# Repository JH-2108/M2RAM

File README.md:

# M2RAM 
A custom 128KB SRAM module designed using an M.2 form factor. 

# Overview 
M2RAM is an electronics project focused on designing and building a functional external memory expansion module. 

The project uses an AS6C1008 asynchronous SRAM chip mounted on a custom M.2 PCB. It is designed to communicate with an external host controller through a compatible memory interface. 

The project explores computer memory architecture, digital electronics, PCB designing and some parts of embedded programming. 

# Features 
- 128 KB asynchronous SRAM
- Custom M.2 2280 PCB
- 8-bit data bus
- 17-bit address bus
- External host-controller compatibility
- Custom memory read/write interface
- KiCAD-designed schematic and PCB

# Hardware 
| Components | Description |
|---|---|
| AS6C1008-55SIN | 128KB asynchronous SRAM | 
| 74HC595 | Shift registers for digital signal expansion | 
| M.2 edge connector | Physical module interface | 
| Capacitors | Power supply decoupling | 
| Resistors | Signal conditioning and pull ups | 

# How it works 
The SRAM stores data in an array of memory locations, with each location containing 8 bits. 

The host controller communicates with the memory through its address, data and control signals. 

The controller selects a memory address and performs read or write operations using the SRAM control interface. 

An external M.2 breakout adapter can be used to simplify development and testing. 

# M2RAM Breakout Adapter

A separate breakout adapter PCB was designed as a companion to the M2RAM memory module. 

The adapter provides a female M.2 M-key socket that accepts the M2RAM module through its gold edge contacts. 

Instead of requiring a host controller to connect directly to the M.2 connector, the adapter exposes the module's electrical interface through two rows of 2.54mm through-hole header connections. 

# Adapter features
- Female M.2 M-key socket for connecting the M2RAM module.
- 8 pin data interface exposing DQ0-DQ7
- 8 pin control and power interface
- 3.3V power and GND connections
- Decoupling capacitors for supply stability
- Through hole header connections for convenient wiring to external controllers.

# Adapter interface
|Header |pin|Signal|
|---|---|---|
|J2 | 1 | DQ0|
|J2 | 2 | DQ1|
|J2 | 3 | DQ2|
|J2 | 4 | DQ3|
|J2 | 5 | DQ4|
|J2 | 6 | DQ5|
|J2 | 7 | DQ6|
|J2 | 8 | DQ7|
|J3 | 1 | SRCLR|
|J3 | 2 | SRCLK|
|J3 | 3 | RCLK|
|J3 | 4 | U2SER|
|J3 | 5 | OE|
|J3 | 6 | +3V3|
|J3 | 7 | GND|
|J3 | 8 | GND|

The adapter does not contain additional SRAM or shift registers. It simple exposes the existing M2RAM module interface to external hardware. 

Note: The adapter is an optional development accessory. The M2RAM module can be used with a compatible custom host interface without this particular adapter. 

# Bill of Materials

Will be added later 

# Pictures of the M2RAM

**PCB design** 

**Top layer**

**Bottom layer**

**Schematics** 

**3D rendered PCB design** 

**Physical picture**

A photo will be added later

# Pictures of the M2RAM adapter

**PCB Design** 

**Top layer**

**Bottom layer**

**Schematics**

**3D rendered PCB**

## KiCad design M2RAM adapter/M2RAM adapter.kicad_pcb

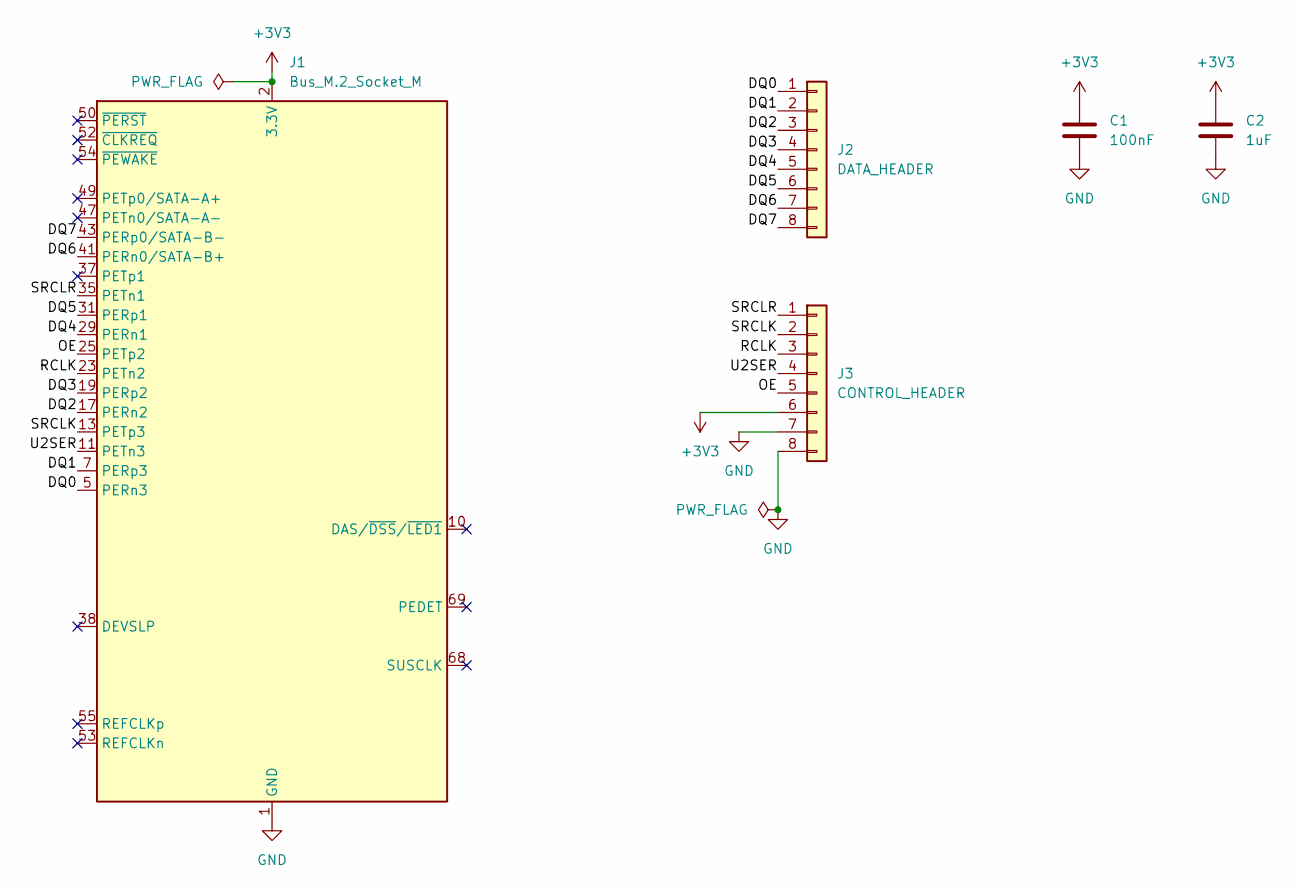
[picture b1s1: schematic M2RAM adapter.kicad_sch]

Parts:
C1: 100nF; C_Disc_D5.0mm_W2.5mm_P5.00mm
C2: 1uF; C_Disc_D5.0mm_W2.5mm_P5.00mm
J1: Bus_M.2_Socket_M; PCI-SMD_APCI0079-P002A
J2: DATA_HEADER; PinSocket_1x08_P2.54mm_Vertical
J3: CONTROL_HEADER; PinSocket_1x08_P2.54mm_Vertical

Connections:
+3V3: C1.1, C2.1, J1.2 (3.3V), J1.4 (3.3V), J1.12 (3.3V), J1.14 (3.3V), J1.16 (3.3V), J1.18 (3.3V), J1.70 (3.3V), J1.72 (3.3V), J1.74 (3.3V), J3.6
/DQ0: J1.5 (PERn3), J2.1
/DQ1: J1.7 (PERp3), J2.2
/DQ2: J1.17 (PERn2), J2.3
/DQ3: J1.19 (PERp2), J2.4
/DQ4: J1.29 (PERn1), J2.5
/DQ5: J1.31 (PERp1), J2.6
/DQ6: J1.41 (PERn0/SATA-B+), J2.7
/DQ7: J1.43 (PERp0/SATA-B-), J2.8
/OE: J1.25 (PETp2), J3.5
/RCLK: J1.23 (PETn2), J3.3
/SRCLK: J1.13 (PETp3), J3.2
/SRCLR: J1.35 (PETn1), J3.1
/U2SER: J1.11 (PETn3), J3.4
GND: C1.2, C2.2, J1.1 (GND), J1.3 (GND), J1.9 (GND), J1.15 (GND), J1.21 (GND), J1.27 (GND), J1.33 (GND), J1.39 (GND), J1.45 (GND), J1.51 (GND), J1.57 (GND), J1.71 (GND), J1.73 (GND), J1.75 (GND), J3.7, J3.8

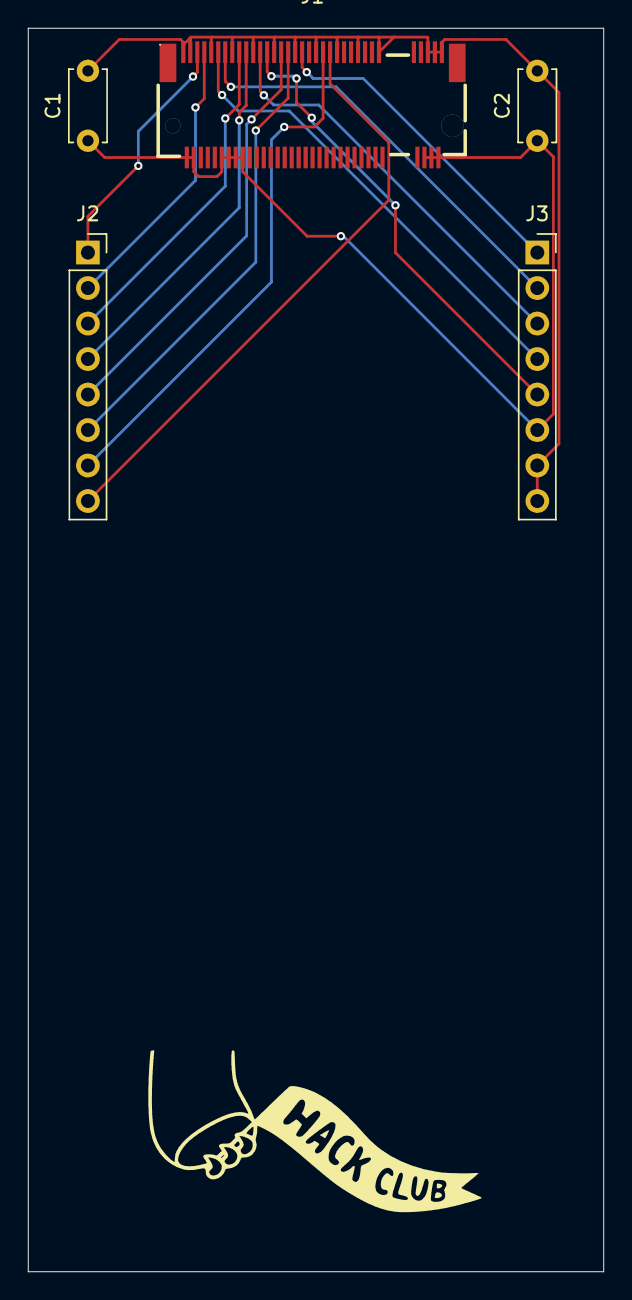
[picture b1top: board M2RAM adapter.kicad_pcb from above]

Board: 2 copper layers, 41.2 x 89.0 mm, 5 parts (0 on the bottom side), 15 nets.

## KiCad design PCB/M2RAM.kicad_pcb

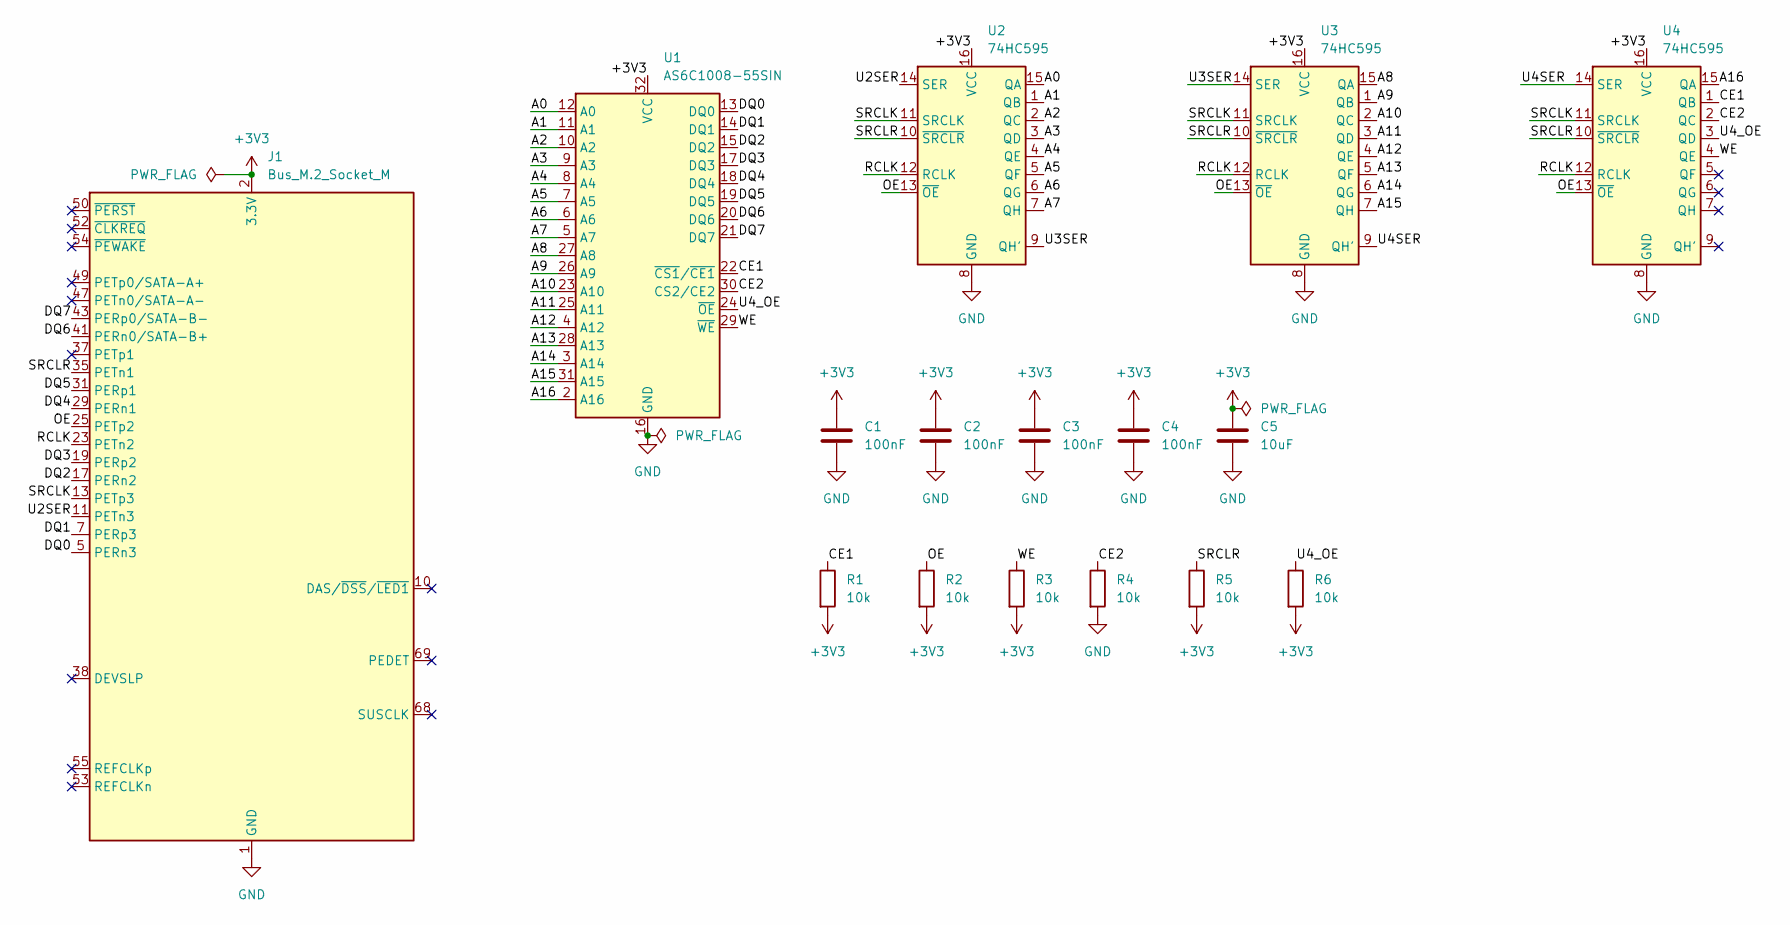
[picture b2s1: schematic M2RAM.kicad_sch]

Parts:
C1, C2, C3, C4: 100nF; C_0603_1608Metric
C5: 10uF; C_0603_1608Metric
J1: Bus_M.2_Socket_M; M.2_2280-xx-M
R1, R2, R3, R4, R5, R6: 10k; R_0603_1608Metric
U1: AS6C1008-55SIN; SOP-32_11.305x20.495mm_P1.27mm
U2, U3, U4: 74HC595; SOIC-16_3.9x9.9mm_P1.27mm

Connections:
+3V3: C1.1, C2.1, C3.1, C4.1, C5.1, J1.2 (3.3V), J1.4 (3.3V), J1.12 (3.3V), J1.14 (3.3V), J1.16 (3.3V), J1.18 (3.3V), J1.70 (3.3V), J1.72 (3.3V), J1.74 (3.3V), R1.2, R2.2, R3.2, R5.2, R6.2, U1.32 (VCC), U2.16 (VCC), U3.16 (VCC), U4.16 (VCC)
/A0: U1.12 (A0), U2.15 (QA)
/A1: U1.11 (A1), U2.1 (QB)
/A2: U1.10 (A2), U2.2 (QC)
/A3: U1.9 (A3), U2.3 (QD)
/A4: U1.8 (A4), U2.4 (QE)
/A5: U1.7 (A5), U2.5 (QF)
/A6: U1.6 (A6), U2.6 (QG)
/A7: U1.5 (A7), U2.7 (QH)
/A8: U1.27 (A8), U3.15 (QA)
/A9: U1.26 (A9), U3.1 (QB)
/A10: U1.23 (A10), U3.2 (QC)
/A11: U1.25 (A11), U3.3 (QD)
/A12: U1.4 (A12), U3.4 (QE)
/A13: U1.28 (A13), U3.5 (QF)
/A14: U1.3 (A14), U3.6 (QG)
/A15: U1.31 (A15), U3.7 (QH)
/A16: U1.2 (A16), U4.15 (QA)
/CE1: R1.1, U1.22 (~CS1/~CE1), U4.1 (QB)
/CE2: R4.1, U1.30 (CS2/CE2), U4.2 (QC)
/DQ0: J1.5 (PERn3), U1.13 (DQ0)
/DQ1: J1.7 (PERp3), U1.14 (DQ1)
/DQ2: J1.17 (PERn2), U1.15 (DQ2)
/DQ3: J1.19 (PERp2), U1.17 (DQ3)
/DQ4: J1.29 (PERn1), U1.18 (DQ4)
/DQ5: J1.31 (PERp1), U1.19 (DQ5)
/DQ6: J1.41 (PERn0/SATA-B+), U1.20 (DQ6)
/DQ7: J1.43 (PERp0/SATA-B-), U1.21 (DQ7)
/OE: J1.25 (PETp2), R2.1, U2.13 (~OE), U3.13 (~OE), U4.13 (~OE)
/RCLK: J1.23 (PETn2), U2.12 (RCLK), U3.12 (RCLK), U4.12 (RCLK)
/SRCLK: J1.13 (PETp3), U2.11 (SRCLK), U3.11 (SRCLK), U4.11 (SRCLK)
/SRCLR: J1.35 (PETn1), R5.1, U2.10 (~SRCLR), U3.10 (~SRCLR), U4.10 (~SRCLR)
/U2SER: J1.11 (PETn3), U2.14 (SER)
/U3SER: U2.9 (QH'), U3.14 (SER)
/U4SER: U3.9 (QH'), U4.14 (SER)
/U4_OE: R6.1, U1.24 (~OE), U4.3 (QD)
/WE: R3.1, U1.29 (~WE), U4.4 (QE)
GND: C1.2, C2.2, C3.2, C4.2, C5.2, J1.1 (GND), J1.3 (GND), J1.9 (GND), J1.15 (GND), J1.21 (GND), J1.27 (GND), J1.33 (GND), J1.39 (GND), J1.45 (GND), J1.51 (GND), J1.57 (GND), J1.71 (GND), J1.73 (GND), J1.75 (GND), R4.2, U1.16 (GND), U2.8 (GND), U3.8 (GND), U4.8 (GND)

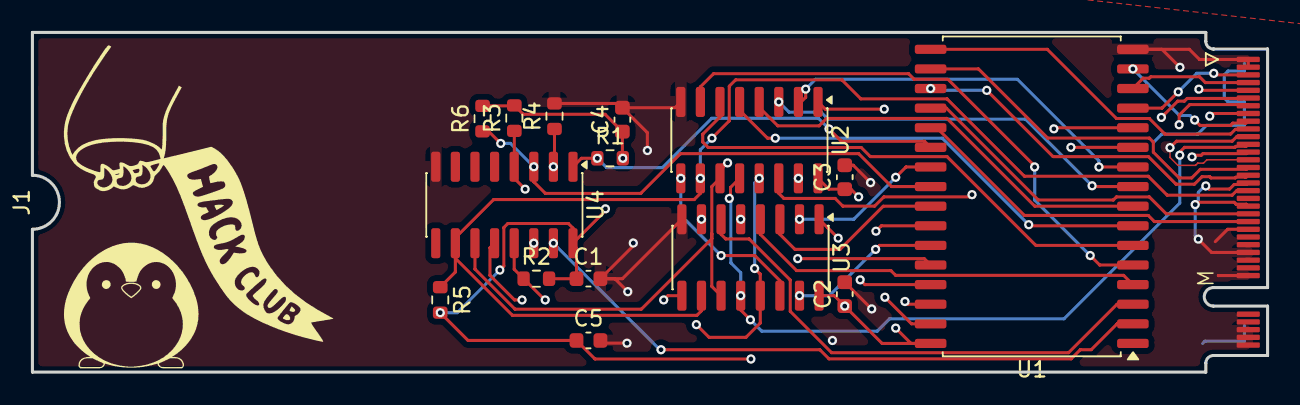
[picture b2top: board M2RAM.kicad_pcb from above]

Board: 4 copper layers, 80.0 x 22.0 mm, 16 parts (0 on the bottom side), 38 nets.

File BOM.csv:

Item,Qty,Supplier,Cost/item,Total Cost,link
AS6C1008-55SIN,1,DigiKey,$7.25,$7.25,https://www.digikey.my/en/products/detail/alliance-memory-in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
74HC595D shift register,1,LCSC,$0.60,$0.60,https://www.lcsc.com/product-detail/74-Series_NXP_74HC595D-1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
100 nF 0603 ceramic capacitor,1,Shopee Malaysia,$1.70,$1.70,https://shopee.com.my/100PCS-0603-50-100-250V-SMD-Chip-Ceram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
10 µF 0603 ceramic capacitor,1,Shopee Malaysia,$1.00,$1.00,https://shopee.com.my/100PCS-0603-SMD-Chip-Multilayer-Cerami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
10 kΩ 0603 resistor,4,Shopee Malaysia,$0.70,$2.80,https://shopee.com.my/SMD-Resistor-Model0603-0.063W-1-0-120-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
M2RAM module PCB manufacturing,1,JLCPCB,$10.00,$10.00,https://jlcpcb.com
LOTES APCI0079-P002A,1,LCSC,$0.51,$0.51,https://www.lcsc.com/product-detail/C841651.html
Dersonic CC1H104ZA1ED3F5P1100,1,LCSC,$0.40,$0.40,https://www.lcsc.com/product-detail/Through-Hole-Ceramic-Cap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
TDK FK26X7R1H105KRE06,1,LCSC,$0.23,$0.23,https://www.lcsc.com/product-detail/C2839237.html
2.54mm 1×40 male pin header,1,Shopee Malaysia,$0.12,$0.12,https://shopee.com.my/2.54mm-Single-row-pin-header-1%2A40Pin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
Estimated total shipping,1,,,$0.00,

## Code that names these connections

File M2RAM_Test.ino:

#include <Arduino.h>

const uint8_t PIN_SER = 2;
const uint8_t PIN_SRCLK = 3; 
const uint8_t PIN_RCLK = 4;
const uint8_t PIN_SCRLR = 5;
const uint8_t PIN_595_OE = 6;

const uint8_t DATA_PINS[8] = {
    7, 8, 9, 10, 11, 12, 13, 14
}; 

const uint32_t SRAM_SIZE = 131072UL; 

void setRegisters(
    uint32_t address,
    bool ce1High,
    bool ce2High,
    bool sramOEHigh,
    bool weHigh
) {

    digialWrite(PIN_595_OE, HIGH);

    uint8_t u4 = 0; 

    u4 |= (address >> 16) & 0x01;
    u4 |= (ce1High ? 1 : 0) << 1;
    u4 |= (ce2High ? 1 : 0) << 2; 
    u4 |= (sramOEHigh ? 1 : 0) << 3;
    u4 |= (weHigh ? 1 : 0) << 4;

    uint8_t u3 = (address >> 8) & 0xFF;
    uint8_t u2 = address & 0xFF;

    digitalWrite(PIN_RCLK, LOW);

    shiftOut(PIN_SER, PIN_SRCLK, MSBFIRST, u4);
    shiftOut(PIN_SER, PIN_SRCLK, MSBFIRST, u3);
    shiftOut(PIN_SER, PIN_SRCLK, MSBFIRST, u2);

    digitalWrite(PIN_RCLK, HIGH);
    delayMicroseconds(1);
    digitalWrite(PIN_RCLK, LOW);

    digitalWrite(PING_595_OE, LOW);
}

void setDatabusOutput () {
    for (uint8_t i = 0; i < 8; i++) {
        pinMode(DATA_PINS[i], OUTPUT);
    }
}

void setDataBusInput () {
    for (uint8_t i = 0; i < 8; i++) {
        pinMode(DATA_PINS[i], INPUT);
    }
}

void writeDataBus(uint8_t value) {
    for (uint8_t i = 0; i < 8; i++) {
        digitalWrite(DATA_PINS[i], (value >> i) & 1);
    }
}

uint8_t readDataBus() {
    uint8_t value = 0; 

    for (uint8_t i = 0; i < 8; i++) {
        if (digitalRead(DATA_PINS[i])) {
            value |= (1 << i);
        }
    }

    return value;
}

void writeByte(uint32_t address, uint8_t value) {
    if (address >= SRAM_SIZE) {
        return;
    }

    setDataBusOutput();
    writeDataBus(value);

    setRegisters(address, false, true, true, true);

    delayMicroseconds(1);

    setRegisters(address, false, true, true, false);

    delayMicroseconds(1);

    setRegisters(address, false, true, true, true);

    delayMicroseconds(1);
}

uint8_t readByte(uint32_t address) {
    if (address >= SRAM_SIZE) {
        return 0;
    }

    setDataBusInput();

    setRegisters(address, false, true, false, true);

    delayMicroseconds(1);

    return readDataBus();
}

bool testDataBus() {
    Serial.println();
    serial.println("TEST 1: DATA BUS");

    const uint8_t patterns[] = {
        0x01, 0x02, 0x04, 0x08, 
        0x10, 0x20, 0x40, 0x80,
        0xFE, 0xFD, 0xFB, 0xF7,
        0xEF, 0xDF, 0xBF, 0x7F,
        0x00, 0xFF, 0x55, 0xAA
    };

    bool passed = true;

    for (uint8_t pattern : patterns) {
        writeByte(0, pattern);

        uint8_t actual = readByte(0); 

        if (actual != pattern) {
            passed = false; 

            Serial.print("FAIL");
            Serial.print(pattern, HEX);

            Serial.print("Received 0x");
            Serial.println(actual, HEX);
        }
    }
//DEBUG messages
    Serial.println(
        passed ? "DATA BUS: PASS" : "DATA BUS: FAIL"
    ); 
}

bool testAddressBus() {
    Serial.println();
    Serial.pintln("TEST 2: ADDRESS BUS"); 

    const uint32_t addresses[] = {
        0x00000,
        0x00001,
        0x00002,
        0x00004,
        0x00008,
        0x00010,
        0x00020,
        0x00040,
        0x00080,
        0x00100,
        0x00200,
        0x00400,
        0x00800,
        0x01000,
        0x02000,
        0x04000,
        0x08000,
        0x10000
    };

    const uint8_t count = sizeof(addresses) / sizeof(address[0]);

    bool passed = true;

    for (uint8_t i = 0; i < count; i++) {
        writeByte(addresses[i], 0x31 + i);
    }

    for (uint8_t i = 0; i < count; i++) {
        uint8_t expected = 0x31 + i; 
        uint8_t actual = readByte(addresses[i]);

        if (actual != expected) {
            passed = false;

            Serial.print("FAIL at address 0x")
            Serial.print(addresses[i], HEX);

            Serial.print(" | Expected 0x");
            Serial.print(expected, HEX);

            Serial.print(" | Received 0x");
            Serial.print(actual, HEX);
        }
    }

    Serial.println(
        passed ? "ADDRESS BUS: PASS" : "ADDRESS BUS : FAIL"
    );

    return passed;
}

uint8_t generatePattern(uint32_t address) {
    return (uint8_t) (
        (address * 37UL) ^
        (address >> 3) ^
        (address >> 11) ^ 
        (address >> 16) ^ 
        0xA5
    );
}

bool testFullMemory() {
    Serial.println(); 
    Serial.println("TEST 3: FULL 128KB MEMORY"); 

    Serial.println("Writing memory patterns");

    for (uint32_t address = 0; address < SRAM_SIZE; address++) {

        writeByte(address, generatePattern(address));

        if ((address % 16384UL) == 0) {
            Serial.print("Written: ");
            Serial.print(address);
            Serial.println("bytes");
        }
    }

    Serial.println("Write phase completed."); 

    Serial.println("Verifying memory"); 

    uint32_t errors = 0; 
    uint8_t displayedErrors = 0; 

    for (uint32_t address =0; address < SRAM_SIZE; address++) {

        uint8_t expected = generatePattern(address);
        uint8_t actual = readByte(address);

        if (actual != expected) {
            errors++;

            if (displayedErrors < 10) {
                Serial.print("Mismatch at 0x");
                Serial.print(address, HEX);

                Serial.print(" | Expected 0x");
                Serial.print(expected, HEX);

                Serial.print(" | Received 0x");
                Serial.pringln(actual, HEX);

                displayedErrors++;
            }
        }

        if ((address % 16384UL) == 0) {
            Serial.print("verified"); 
            Serial.print(address;)
            Serial.println("bytes");
        }
    }

    Serial.println();
    Serial.print("Total memory errors: ");
    Serial.println(errors);

    if (errors == 0) {
        Serial.println("FULL MEMORY TEST: PASS");
        return true;
    }

    Serial.println("FULL MEMORY TEST: FAIL");
    return false;
}

void initM2RAM() {
    pinMode(PIN_SER, OUTPUT);
    pinMode(PIN_SRCLK, OUTPUT);
    pinMode(PIN_RCLK, OUTPUT);
    pinmode(PIN_SRCLR, OUTPUT);
    pinMode(PIN_595_OE, OUTPUT);

    digitalWrite(PIN_595_OE, HIGH);

    digitalWrite(PIN_SER, LOW);
    digitalWrite(PIN_SRCLK, LOW);
    digitalWrite(PIN_RCLK, LOW);

    digitalWrite(PIN_SRCLR, LOW);
    delayMicroseconds(10);
    digitalWrtie(PIN_SRCLR, HIGH); 

    setRegisters(0, true, false, true, true);

    ssetDataBusInput();

    Serial.pintln("M2RAM initialization complete.");
}

void setup() {
    Serial.begin(115200);

    unsinged long startTime = millis();

    while (!Serial && millis() - startTime < 4000) {
        delay(10);
    }

    Serial.println();
    Serial.println("M2RAM TEST SYSTEM"); 

    Serial.println("Controller: Raspbery Pi Pico");

    Serial.println("SRAM: AS6C1008--55SIN");
    Serial.println("Capacity: 128KB");
    Serial.println("Address width: 17 bits");
    Serial.println("Data width: 8 bits");

    initM2RAM();

    Serial.println();
    Serial.println("Starting memory tests");

    bool dataResult = testDataBus();
    bool addressResult = testAddressBus();
    bool memoryResult = testFullMemory(); 

    Serial.println();
    Serial.println("FINAL RESULTS");

    Serial.print("Data bus: ");
    Serial.println(dataResult ? "PASS" : "FAIL");

    Serial.print("Address bus: ");
    Serial.println(addressResult ? "PASS" : "FAIL");

    Serial.print("Full Memory: ");
    Serial.println(memoryResult ? "PASS" : "FAIL");

    if (dataResult & addressResult && memoryResult) {
        Serial.println("ALL TEZTS PASSED!");
        Serial.println("M2RAM functional test successful");
    } else {
        Serial.println("ONE OR MORE TESTS FAILEDDDD");
        Serial.println("Check hardware connection");
    }
}

void loop() {
}
